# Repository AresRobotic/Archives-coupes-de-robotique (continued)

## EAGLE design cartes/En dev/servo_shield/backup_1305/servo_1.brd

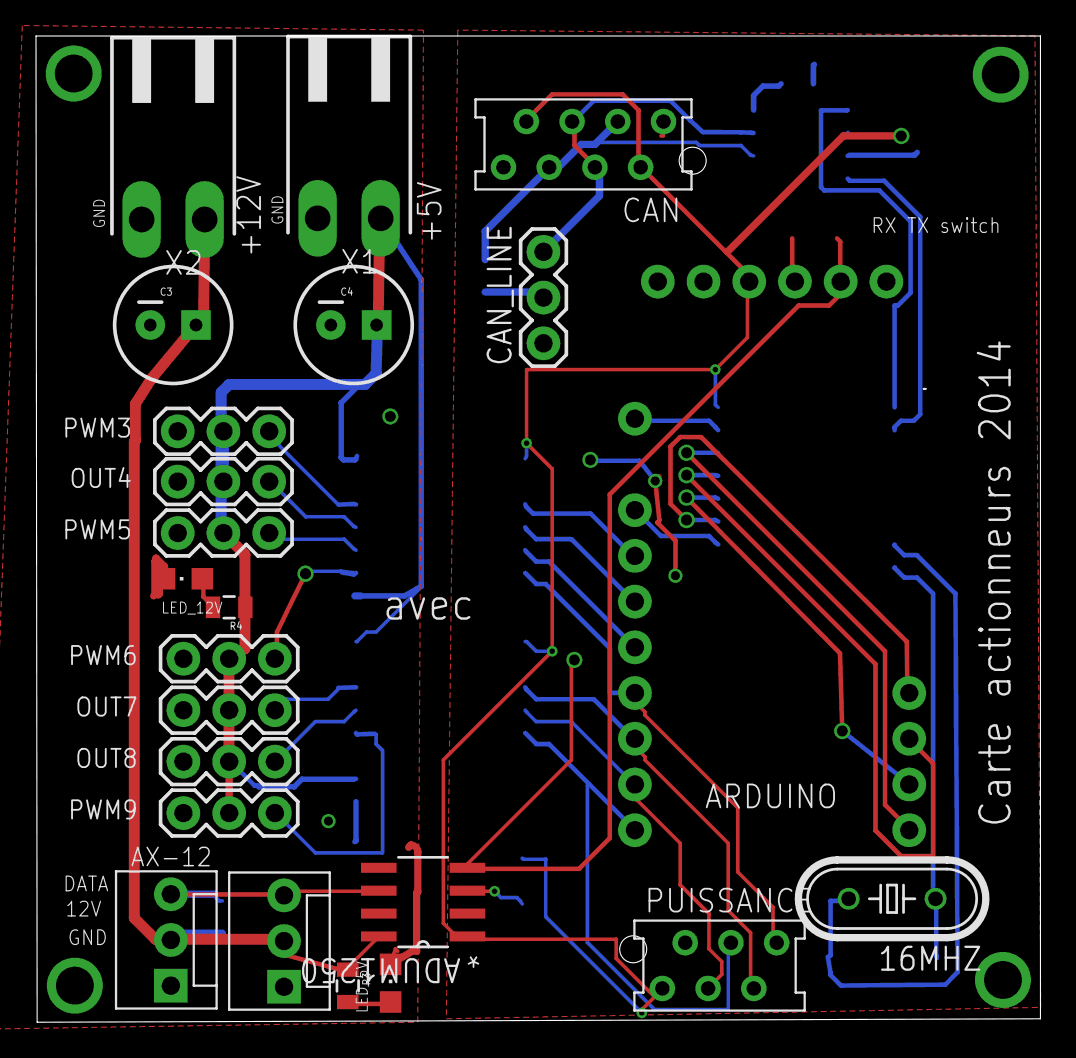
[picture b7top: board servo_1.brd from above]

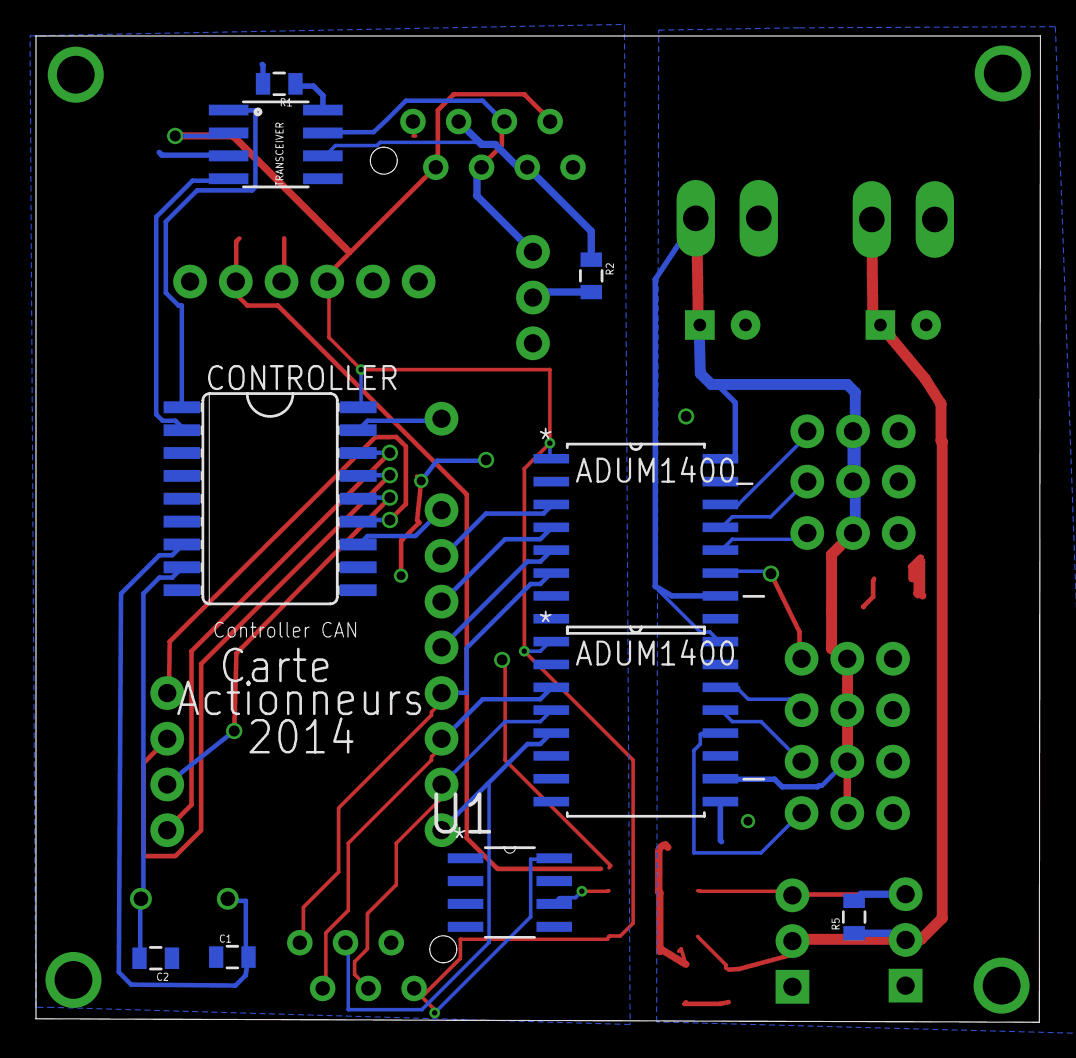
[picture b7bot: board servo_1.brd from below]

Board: 2 copper layers, 55.8 x 54.8 mm, 33 parts (10 on the bottom side), 37 nets.

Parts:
16MHZ: 16MHz; HC49/S
ADUM1250: ADUM1250ARZ; SOIC127P600X175-8N
ADUM1400, ADUM1400_: ADUM1400ARWZ; SOIC127P1032X265-16N
ARDUINO: ARDUINO_PRO_MINI'SERVO; ARDUINO_PRO_MINI
C1, C2: 22pF; 0805
C3, C4: 100uF; CPOL-RADIAL-100UF-25V
CAN: AMP-215079-8
CAN_LINE: JUMPER-3PTH; 1X03
CONTROLLER: MCP2515SO; SO18L
JP2: AX-12_1; MOLEX-1X3
JP4: AX-12_2; MOLEX-1X3
LED_5V, LED_12V: CHIPLED_0805
OUT4: PWM4; 1X03
OUT7: PWM7; 1X03
OUT8: servo_option_1; 1X03
PUISSANCE: MMATCH-6-; AMP-215079-6
PWM3: PWM3; 1X03
PWM5: PWM5; 1X03
PWM6: servo_option; 1X03
PWM9: servo_option_2; 1X03
R1: 4,7k; 0805
R2: 120; 0805
R3, R4: 1k; 0805
R5: 10k; 0805
TRANSCEIVER: MCP2551; SO08
U1: SN65HVD08D; SOIC127P600X175-8N
X1: 5V_INPUT; 90-2
X2: 12V_INPUT; 90-2

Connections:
5V_DIRTY: ADUM1400.10, ADUM1400.16, ADUM1400_.10, ADUM1400_.16, C4.1, OUT4.2, OUT7.2, OUT8.2, PWM3.2, PWM5.2, PWM6.2, PWM9.2, R4.1, X1.1
12V_DIRTY: ADUM1250.8, C3.1, JP2.2, JP4.2, R3.1, R5.1, X2.1
CANH: CAN.4, CAN.5, CAN_LINE.3, TRANSCEIVER.7
CANL: CAN.3, CAN.6, R2.1, TRANSCEIVER.6
CAN_CS: ARDUINO.13, CONTROLLER.16
CAN_INT: ARDUINO.5, CONTROLLER.12
CAN_RXD: CONTROLLER.2, TRANSCEIVER.4
CAN_TXD: CONTROLLER.1, TRANSCEIVER.1
GND: ADUM1250.4, ADUM1400.2, ADUM1400.8, ADUM1400_.2, ADUM1400_.8, ARDUINO.GND, C1.1, C2.1, CAN.1, CAN.8, CONTROLLER.9, PUISSANCE.2, R1.2, TRANSCEIVER.3, U1.5
GND_DIRTY: ADUM1250.5, ADUM1400.9, ADUM1400.15, ADUM1400_.9, ADUM1400_.15, C3.2, C4.2, JP2.1, JP4.1, LED_5V.C, LED_12V.C, OUT4.3, OUT7.3, OUT8.3, PWM3.3, PWM5.3, PWM6.3, PWM9.3, X1.2, X2.2
MISO: ARDUINO.15, CONTROLLER.15
MOSI: ARDUINO.14, CONTROLLER.14
unnamed: 16MHZ.2, C1.2, CONTROLLER.7
unnamed: 16MHZ.1, C2.2, CONTROLLER.8
unnamed: LED_5V.A, R3.2
unnamed: R1.1, TRANSCEIVER.8
unnamed: LED_12V.A, R4.2
unnamed: CAN_LINE.2, R2.2
OUT4: ADUM1400_.4, ARDUINO.7
OUT7: ADUM1400.3, ARDUINO.10, PUISSANCE.5
OUT8: ADUM1400.4, ARDUINO.11, PUISSANCE.3
PWM3: ADUM1400_.3, ARDUINO.6
PWM3_OUT: ADUM1400_.14, PWM3.1
PWM4_OUT: ADUM1400_.13, OUT4.1
PWM5: ADUM1400_.5, ARDUINO.8
PWM5_OUT: ADUM1400_.12, PWM5.1
PWM6: ADUM1400_.6, ARDUINO.9, PUISSANCE.6
PWM6_OUT: ADUM1400_.11, PWM6.1
PWM7_OUT: ADUM1400.14, OUT7.1
PWM8_OUT: ADUM1400.13, OUT8.1
PWM9: ADUM1400.5, ARDUINO.12, PUISSANCE.4
PWM9_OUT: ADUM1400.12, PWM9.1
RST: ARDUINO.3, CONTROLLER.17
RXTX: ADUM1250.3, U1.6
RXTX_DIRTY: ADUM1250.6, JP2.3, JP4.3, R5.2
SCK: ARDUINO.16, CONTROLLER.13
VCC: ADUM1250.1, ADUM1400.1, ADUM1400_.1, ARDUINO.VCC, CAN.2, CAN.7, CONTROLLER.18, PUISSANCE.1, TRANSCEIVER.2, U1.8
